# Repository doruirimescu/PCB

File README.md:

# PCB
Printed circuit board projects

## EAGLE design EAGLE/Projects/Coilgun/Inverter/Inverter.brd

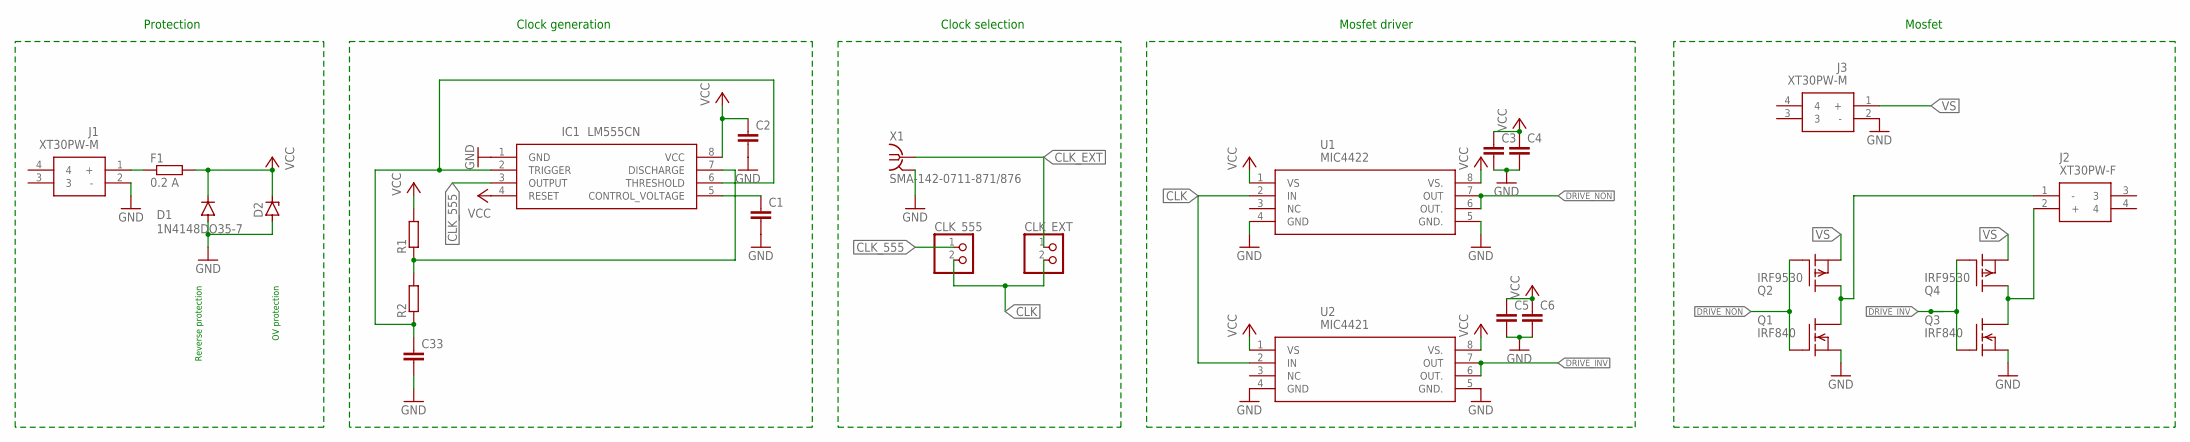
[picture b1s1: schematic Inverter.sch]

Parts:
C1: C-EU025-050X050; C025-050X050
C2, C3, C4, C5, C6, C33: C-EUC0805; C0805
CLK_555: PINHD-1X2; 1X02
CLK_EXT: PINHD-1X2; 1X02
D1: 1N4148DO35-7; DO35-7
D2: ZENER-DIODEDO35Z10; DO35Z10
F1: 0.2 A; M1206
IC1: LM555CN; DIP762W53P254L980H533Q8N
J1, J3: XT30PW-M; XT30PWM
J2: XT30PW-F; XT30PWF
Q1, Q3: IRF840; TO220
Q2, Q4: IRF9530; TO220
R1, R2: R-EU_M0805; M0805
U1: MIC4422; MIC4421
U2: MIC4421
X1: SMA-142-0711-871/876; J502-ND-142-0711-871/876

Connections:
CLK: CLK_555.2, CLK_EXT.2, U1.2 (IN), U2.2 (IN)
CLK_555: CLK_555.1, IC1.3 (OUTPUT)
CLK_EXT: CLK_EXT.1, X1.1
DRIVE_INV: Q3.1 (G), Q4.1 (G), U2.6 (OUT.), U2.7 (OUT)
DRIVE_NON: Q1.1 (G), Q2.1 (G), U1.6 (OUT.), U1.7 (OUT)
GND: C1.2, C2.2, C3.2, C4.2, C5.2, C6.2, C33.2, D1.A, D2.A, IC1.1 (GND), J1.2 (-), J3.2 (-), Q1.3 (S), Q3.3 (S), U1.4 (GND), U1.5 (GND.), U2.4 (GND), U2.5 (GND.), X1.G@1 (2), X1.G@2 (2), X1.G@3 (2), X1.G@4 (2)
unnamed: C33.1, IC1.2 (TRIGGER), IC1.6 (THRESHOLD), R2.1
unnamed: IC1.7 (DISCHARGE), R1.1, R2.2
unnamed: C1.1, IC1.5 (CONTROL_VOLTAGE)
unnamed: J2.1 (-), Q1.2 (D), Q2.2 (D)
unnamed: J2.2 (+), Q3.2 (D), Q4.2 (D)
unnamed: F1.1, J1.1 (+)
VCC: C2.1, C3.1, C4.1, C5.1, C6.1, D1.C, D2.C, F1.2, IC1.4 (RESET), IC1.8 (VCC), R1.2, U1.1 (VS), U1.8 (VS.), U2.1 (VS), U2.8 (VS.)
VS: J3.1 (+), Q2.3 (S), Q4.3 (S)

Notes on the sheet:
Clock generation
Clock selection
Protection
Reverse protection
OV protection
Mosfet driver
Mosfet

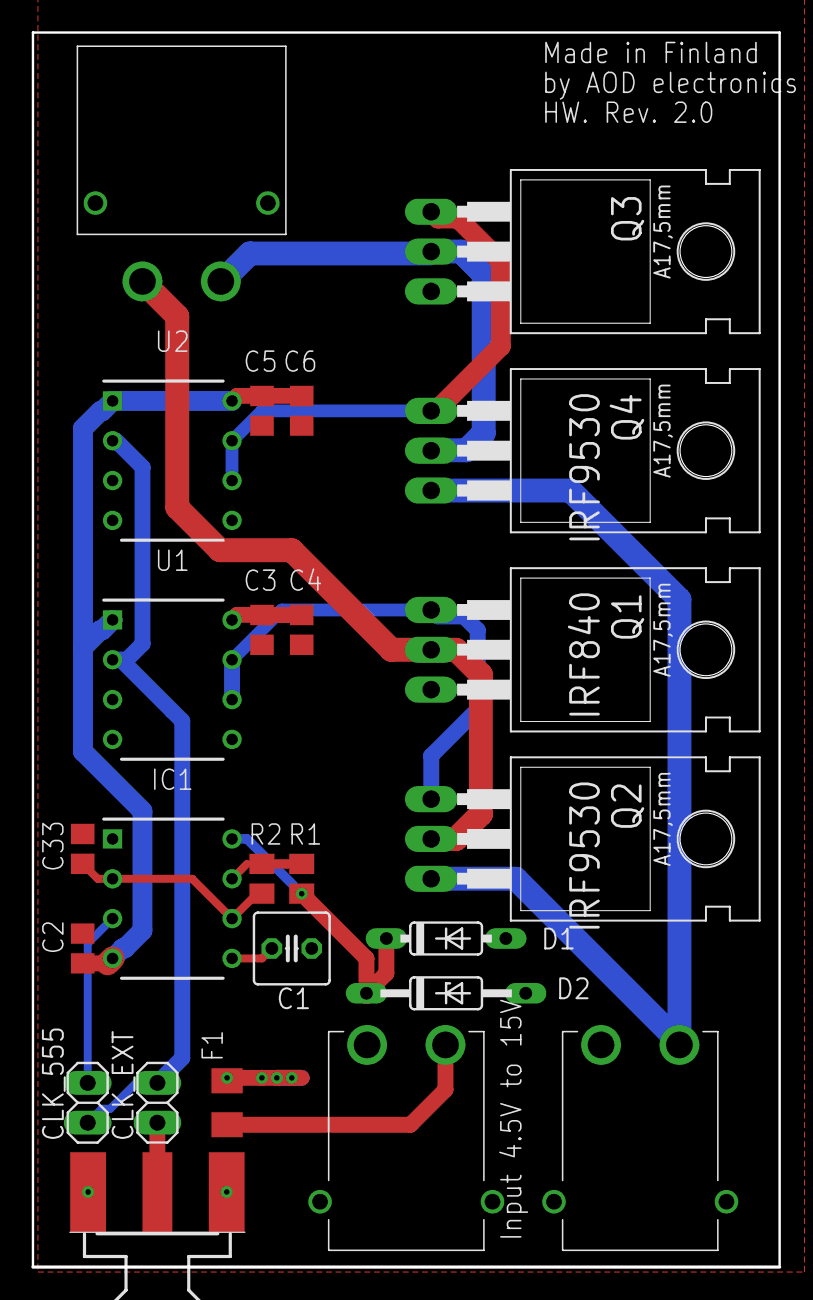
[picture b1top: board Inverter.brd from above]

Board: 2 copper layers, 47.6 x 78.7 mm, 25 parts (0 on the bottom side), 14 nets.

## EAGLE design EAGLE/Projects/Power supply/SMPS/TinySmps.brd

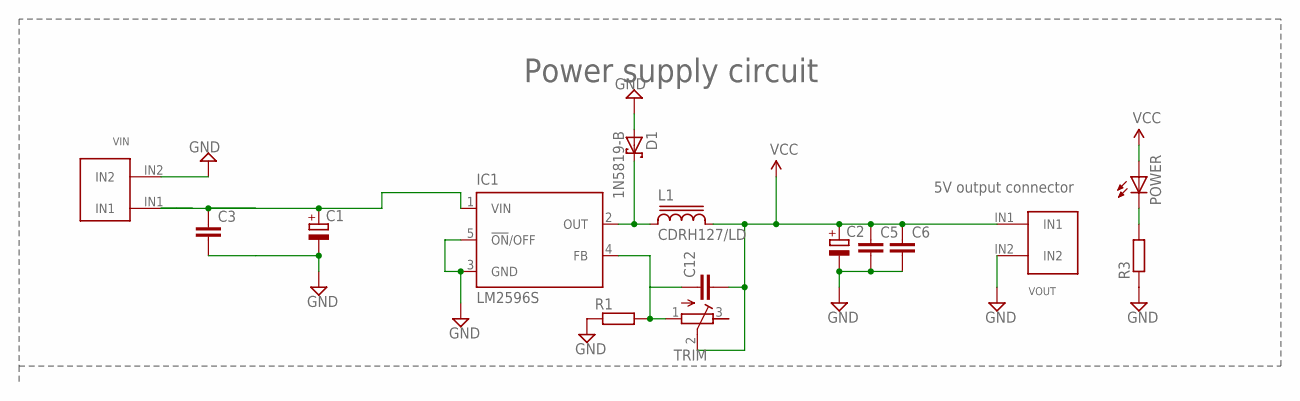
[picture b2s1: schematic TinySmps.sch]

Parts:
C1, C2: CPOL-EUE5-10.5; E5-10,5
C3, C5, C6: C-EUC1206; C1206
C12: C2,5-3; C2.5-3
D1: 1N5819-B; DO41-7.6
IC1: LM2596S; TO263-5
L1: CDRH127/LD
POWER: LEDSML0805; SML0805
R1: R-EU_0204/7; 0204/7
R3: R-EU_R1206; R1206
TRIM: R-TRIMM3296W; RTRIM3296W
VIN: 1X2_5MM
VOUT: 1X2_5MM

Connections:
GND: C1.-, C2.-, C3.2, C5.2, C6.2, D1.A, IC1.3 (GND), IC1.5 (!ON!/OFF), R1.1, R3.1, VIN.IN2, VOUT.IN2
IN: C1.+, C3.1, IC1.1 (VIN), VIN.IN1
unnamed: POWER.C, R3.2
unnamed: D1.C, IC1.2 (OUT), L1.1
unnamed: C12.1, IC1.4 (FB), R1.2, TRIM.1 (A)
VCC: C2.+, C5.1, C6.1, C12.2, L1.2, POWER.A, TRIM.2 (S), VOUT.IN1

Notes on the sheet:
Power supply circuit
5V output connector

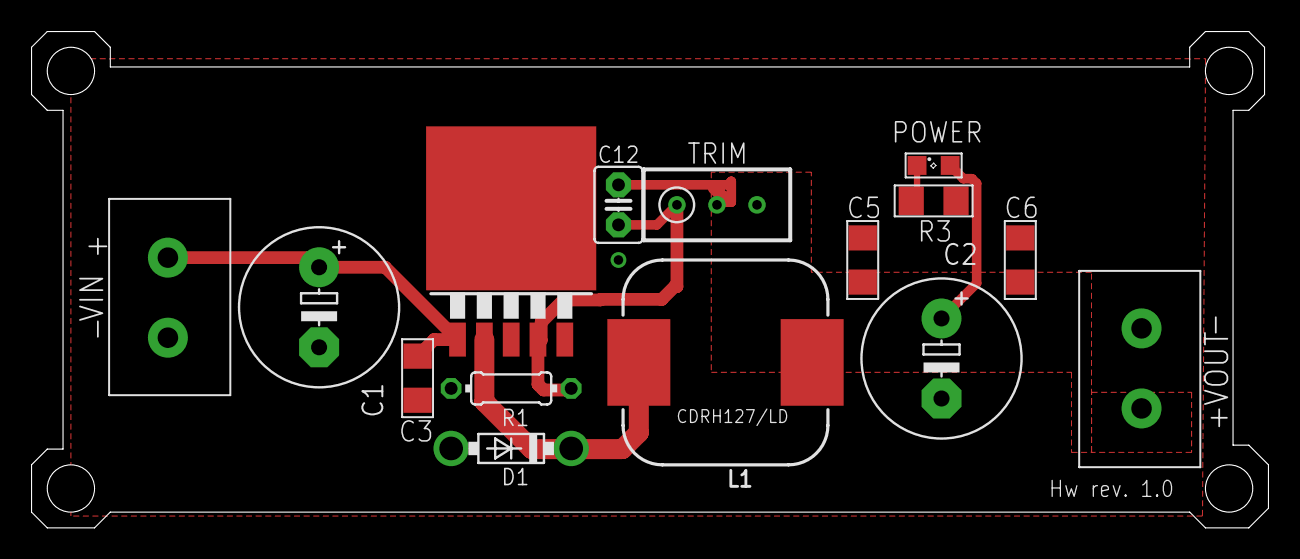
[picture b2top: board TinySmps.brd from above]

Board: 2 copper layers, 78.5 x 31.5 mm, 15 parts (0 on the bottom side), 6 nets.

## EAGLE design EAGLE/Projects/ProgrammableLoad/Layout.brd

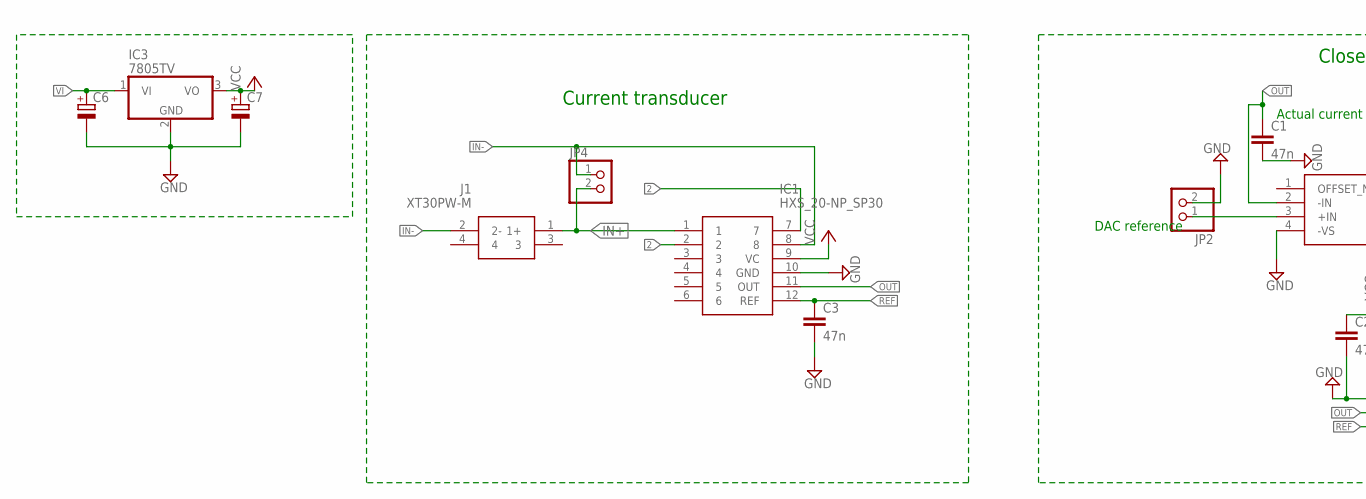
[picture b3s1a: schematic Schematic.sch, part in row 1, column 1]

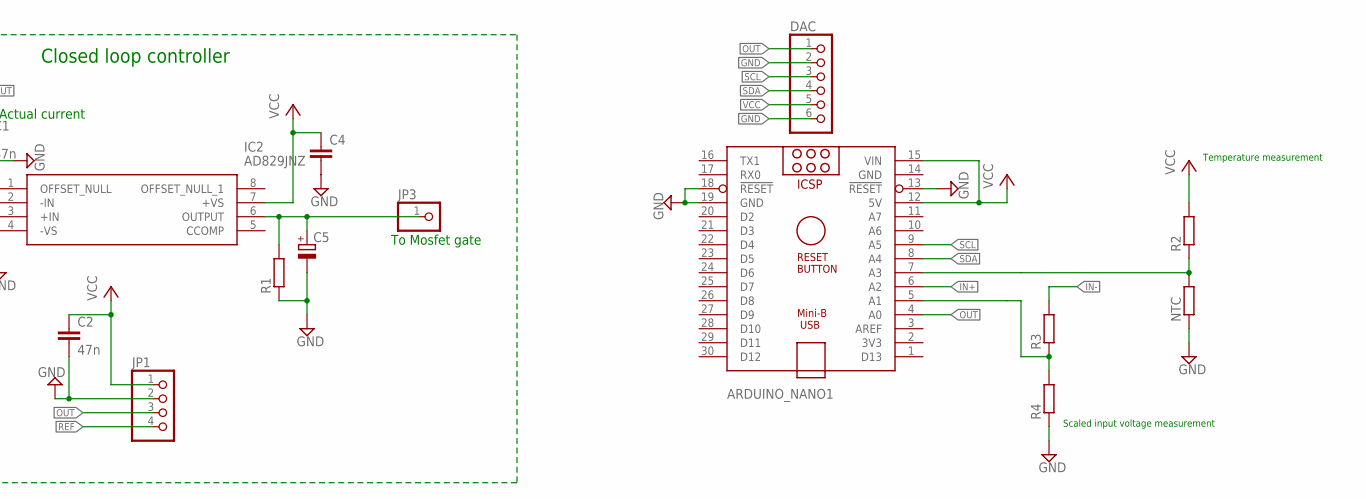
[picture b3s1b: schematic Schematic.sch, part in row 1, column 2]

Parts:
ARDUINO_NANO1: ARDUINO_NANO
C1, C2, C3: 47n; C2.5-6
C4: C-EUC0805; C0805
C5: CPOL-EUE5-6; E5-6
C6, C7: CPOL-EUE2.5-5; E2,5-5
DAC: PINHD-1X6; 1X06
IC1: HXS_20-NP_SP30; HXS_20-NP/SP30
IC2: AD829JNZ; DIP794W56P254L959H533Q8N
IC3: 7805TV; TO220V
J1: XT30PW-M; XT30PWM
JP1: PINHD-1X4; 1X04
JP2, JP4: PINHD-1X2; 1X02
JP3: PINHD-1X1; 1X01
NTC: R0207/10; 0207/10
R1, R2: R0207/10; 0207/10
R3, R4: R-EU_R1206; R1206

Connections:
2: IC1.2, IC1.7
GND: ARDUINO_NANO1.13 (!RESET), ARDUINO_NANO1.14 (GND), ARDUINO_NANO1.18 (!RESET), ARDUINO_NANO1.19 (GND), C1.2, C2.2, C3.2, C4.2, C5.-, C6.-, C7.-, DAC.2, DAC.6, IC1.10 (GND), IC2.4 (-VS), IC3.2 (GND), JP1.2, JP2.2, NTC.1, R1.1, R4.1
IN+: ARDUINO_NANO1.6 (A2), IC1.1, J1.1 (1+), JP4.2
IN-: IC1.8, J1.2 (2-), JP4.1, R3.2
unnamed: C5.+, IC2.6 (OUTPUT), JP3.1, R1.2
unnamed: ARDUINO_NANO1.5 (A1), R3.1, R4.2
unnamed: IC2.3 (+IN), JP2.1
unnamed: ARDUINO_NANO1.7 (A3), NTC.2, R2.1
OUT: ARDUINO_NANO1.4 (A0), C1.1, DAC.1, IC1.11 (OUT), IC2.2 (-IN), JP1.3
REF: C3.1, IC1.12 (REF), JP1.4
SCL: ARDUINO_NANO1.9 (A5), DAC.3
SDA: ARDUINO_NANO1.8 (A4), DAC.4
VCC: ARDUINO_NANO1.12 (5V), ARDUINO_NANO1.15 (VIN), C2.1, C4.1, C7.+, DAC.5, IC1.9 (VC), IC2.7 (+VS), IC3.3 (VO), JP1.1, R2.2
VI: C6.+, IC3.1 (VI)

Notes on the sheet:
DAC reference
Actual current
To Mosfet gate
Current transducer
Closed loop controller
Temperature measurement
Scaled input voltage measurement

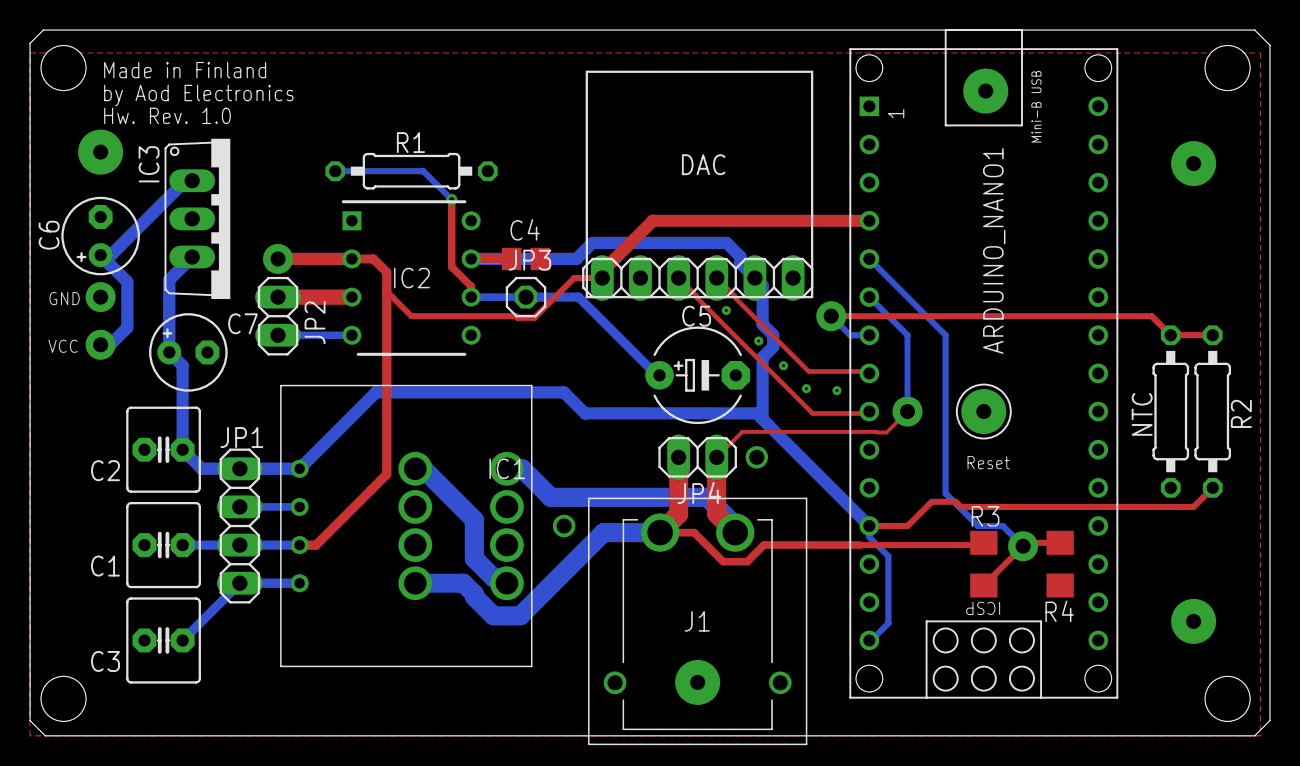
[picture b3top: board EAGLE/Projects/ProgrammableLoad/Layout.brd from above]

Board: 2 copper layers, 82.5 x 47.0 mm, 22 parts (0 on the bottom side), 14 nets.

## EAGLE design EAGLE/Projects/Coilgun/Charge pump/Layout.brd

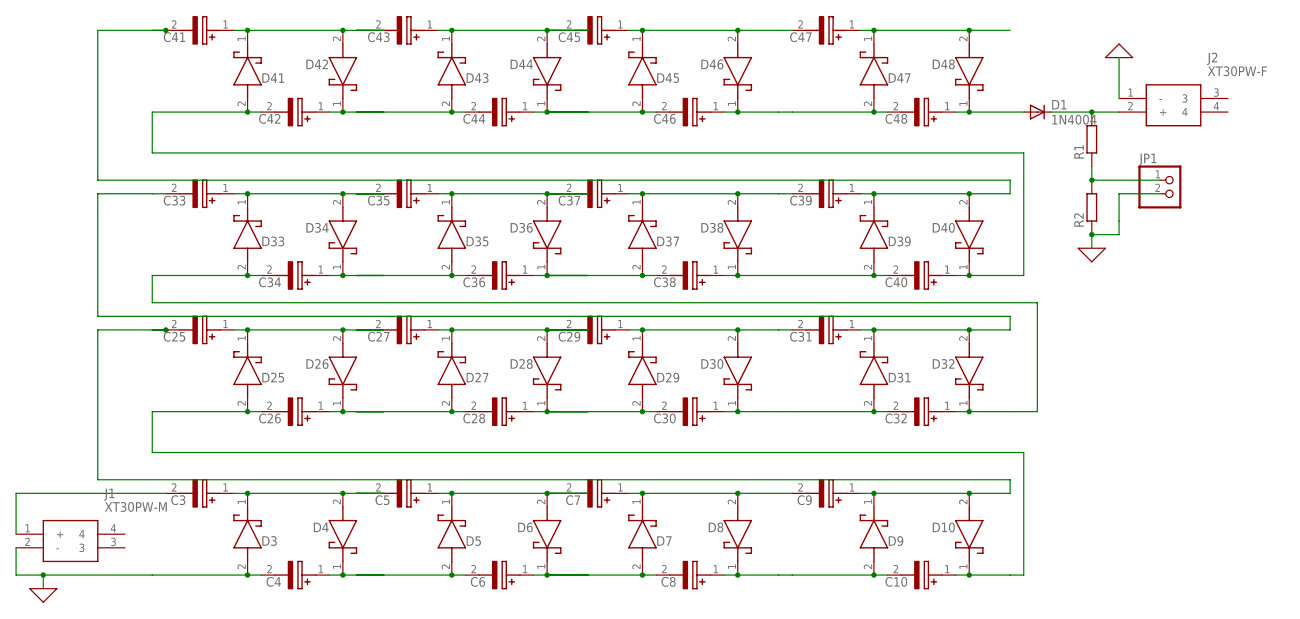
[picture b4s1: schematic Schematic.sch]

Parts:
C3, C4, C5, C6, C7, C8, C9, C10, C25, C26, C27, C28, C29, C30, C31, C32, C33, C34, C35, C36, C37, C38, C39, C40, C41, C42, C43, C44, C45, C46, C47, C48: AFK108M25H32T-F; CAPAE1350X1400N
D1: 1N4004; DO41-10
D3, D4, D5, D6, D7, D8, D9, D10, D25, D26, D27, D28, D29, D30, D31, D32, D33, D34, D35, D36, D37, D38, D39, D40, D41, D42, D43, D44, D45, D46, D47, D48: PMEG3050EP,115; PMEG3050EP115
J1: XT30PW-M; XT30PWM
J2: XT30PW-F; XT30PWF
JP1: PINHD-1X2; 1X02
R1, R2: RR0603; R0603

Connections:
0: C4.2 (-), D3.2 (A), J1.2 (-), J2.1 (-), JP1.2, R2.1
unnamed: D1.C, J2.2 (+), R1.2
unnamed: JP1.1, R1.1, R2.2
unnamed: C3.1 (+), C5.2 (-), D3.1 (K), D4.2 (A)
unnamed: C3.2 (-), J1.1 (+)
unnamed: C5.1 (+), C7.2 (-), D5.1 (K), D6.2 (A)
unnamed: C4.1 (+), C6.2 (-), D4.1 (K), D5.2 (A)
unnamed: C6.1 (+), C8.2 (-), D6.1 (K), D7.2 (A)
unnamed: C9.1 (+), C25.2 (-), D9.1 (K), D10.2 (A)
unnamed: C8.1 (+), C10.2 (-), D8.1 (K), D9.2 (A)
unnamed: C10.1 (+), C26.2 (-), D10.1 (K), D25.2 (A)
unnamed: C7.1 (+), C9.2 (-), D7.1 (K), D8.2 (A)
unnamed: C33.1 (+), C35.2 (-), D33.1 (K), D34.2 (A)
unnamed: C25.1 (+), C27.2 (-), D25.1 (K), D26.2 (A)
unnamed: C31.1 (+), C33.2 (-), D31.1 (K), D32.2 (A)
unnamed: C35.1 (+), C37.2 (-), D35.1 (K), D36.2 (A)
unnamed: C27.1 (+), C29.2 (-), D27.1 (K), D28.2 (A)
unnamed: C26.1 (+), C28.2 (-), D26.1 (K), D27.2 (A)
unnamed: C28.1 (+), C30.2 (-), D28.1 (K), D29.2 (A)
unnamed: C30.1 (+), C32.2 (-), D30.1 (K), D31.2 (A)
unnamed: C32.1 (+), C34.2 (-), D32.1 (K), D33.2 (A)
unnamed: C29.1 (+), C31.2 (-), D29.1 (K), D30.2 (A)
unnamed: C34.1 (+), C36.2 (-), D34.1 (K), D35.2 (A)
unnamed: C36.1 (+), C38.2 (-), D36.1 (K), D37.2 (A)
unnamed: C39.1 (+), C41.2 (-), D39.1 (K), D40.2 (A)
unnamed: C38.1 (+), C40.2 (-), D38.1 (K), D39.2 (A)
unnamed: C40.1 (+), C42.2 (-), D40.1 (K), D41.2 (A)
unnamed: C37.1 (+), C39.2 (-), D37.1 (K), D38.2 (A)
unnamed: C41.1 (+), C43.2 (-), D41.1 (K), D42.2 (A)
unnamed: C43.1 (+), C45.2 (-), D43.1 (K), D44.2 (A)
unnamed: C42.1 (+), C44.2 (-), D42.1 (K), D43.2 (A)
unnamed: C44.1 (+), C46.2 (-), D44.1 (K), D45.2 (A)
unnamed: C47.1 (+), D47.1 (K), D48.2 (A)
unnamed: C46.1 (+), C48.2 (-), D46.1 (K), D47.2 (A)
unnamed: C48.1 (+), D1.A, D48.1 (K)
unnamed: C45.1 (+), C47.2 (-), D45.1 (K), D46.2 (A)

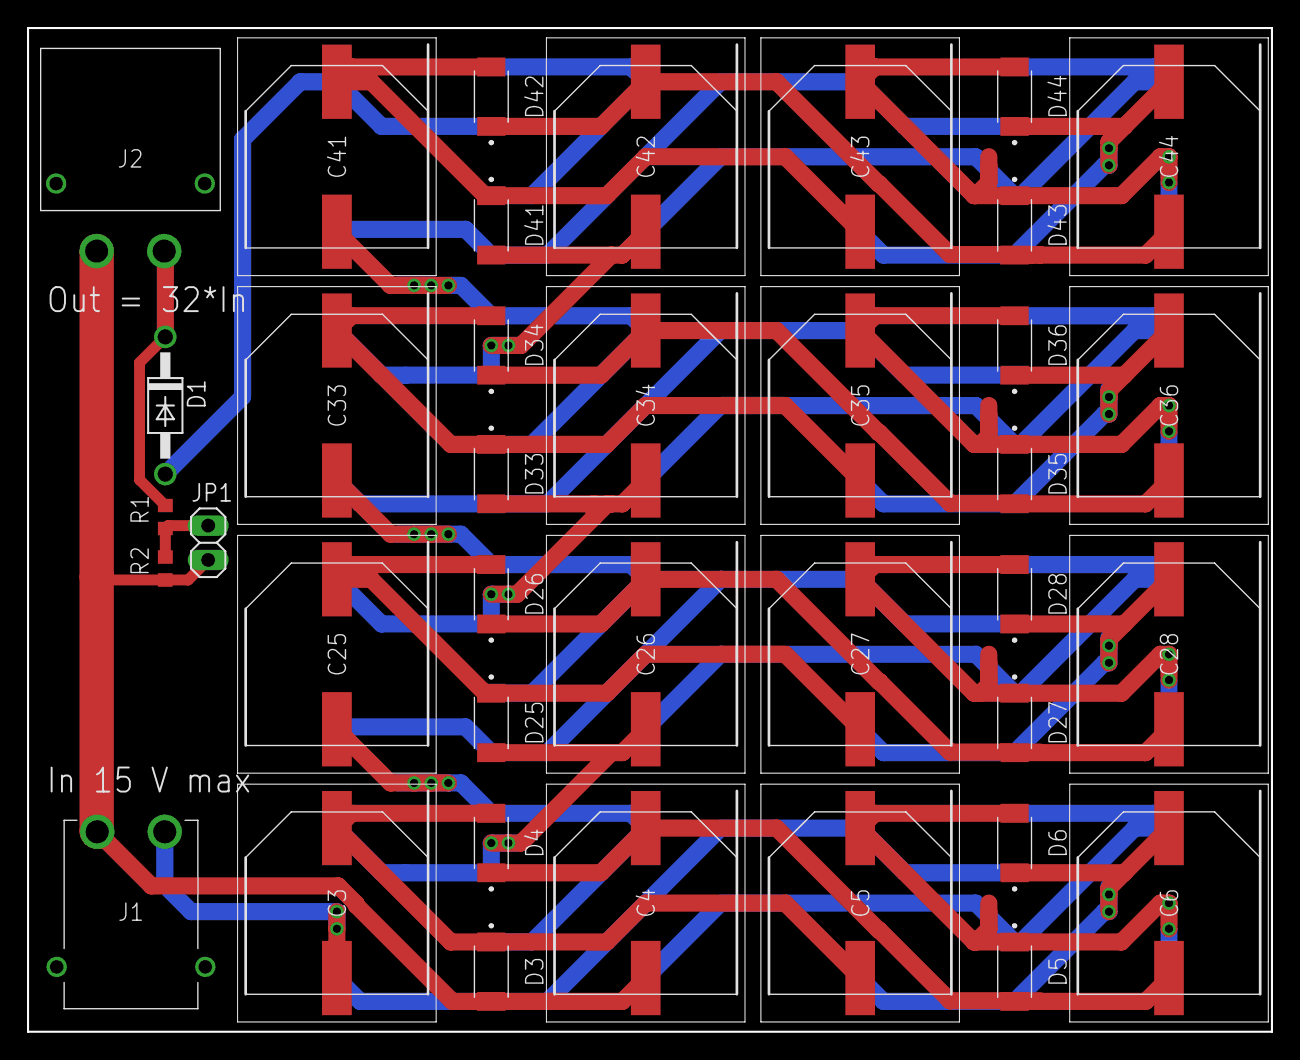
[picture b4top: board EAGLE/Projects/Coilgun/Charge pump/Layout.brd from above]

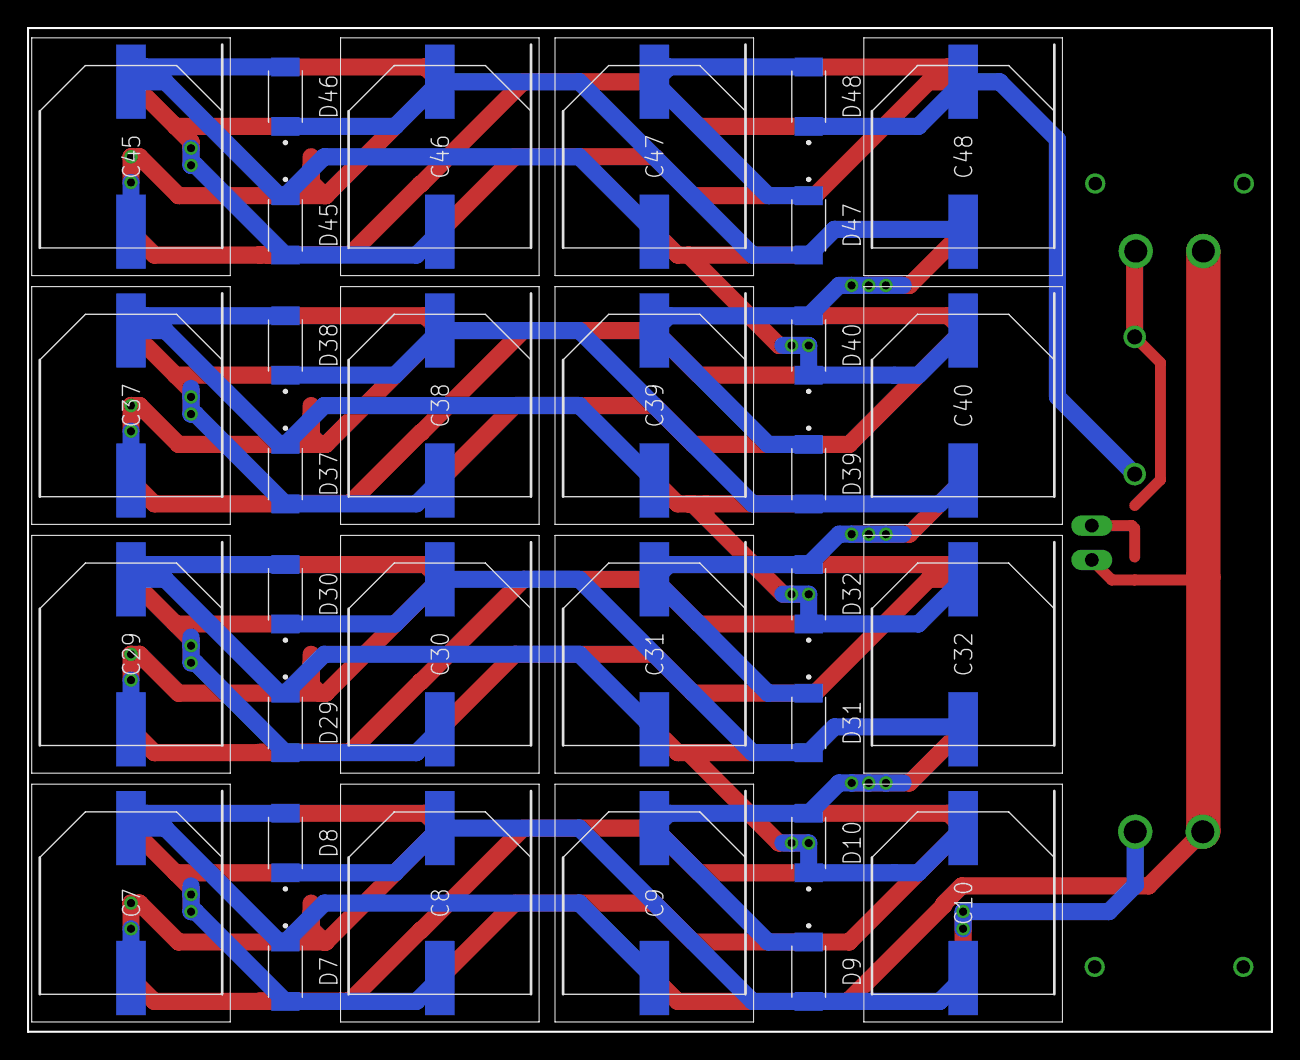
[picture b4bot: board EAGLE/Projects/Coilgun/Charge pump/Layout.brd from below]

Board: 2 copper layers, 92.1 x 74.3 mm, 70 parts (32 on the bottom side), 36 nets.

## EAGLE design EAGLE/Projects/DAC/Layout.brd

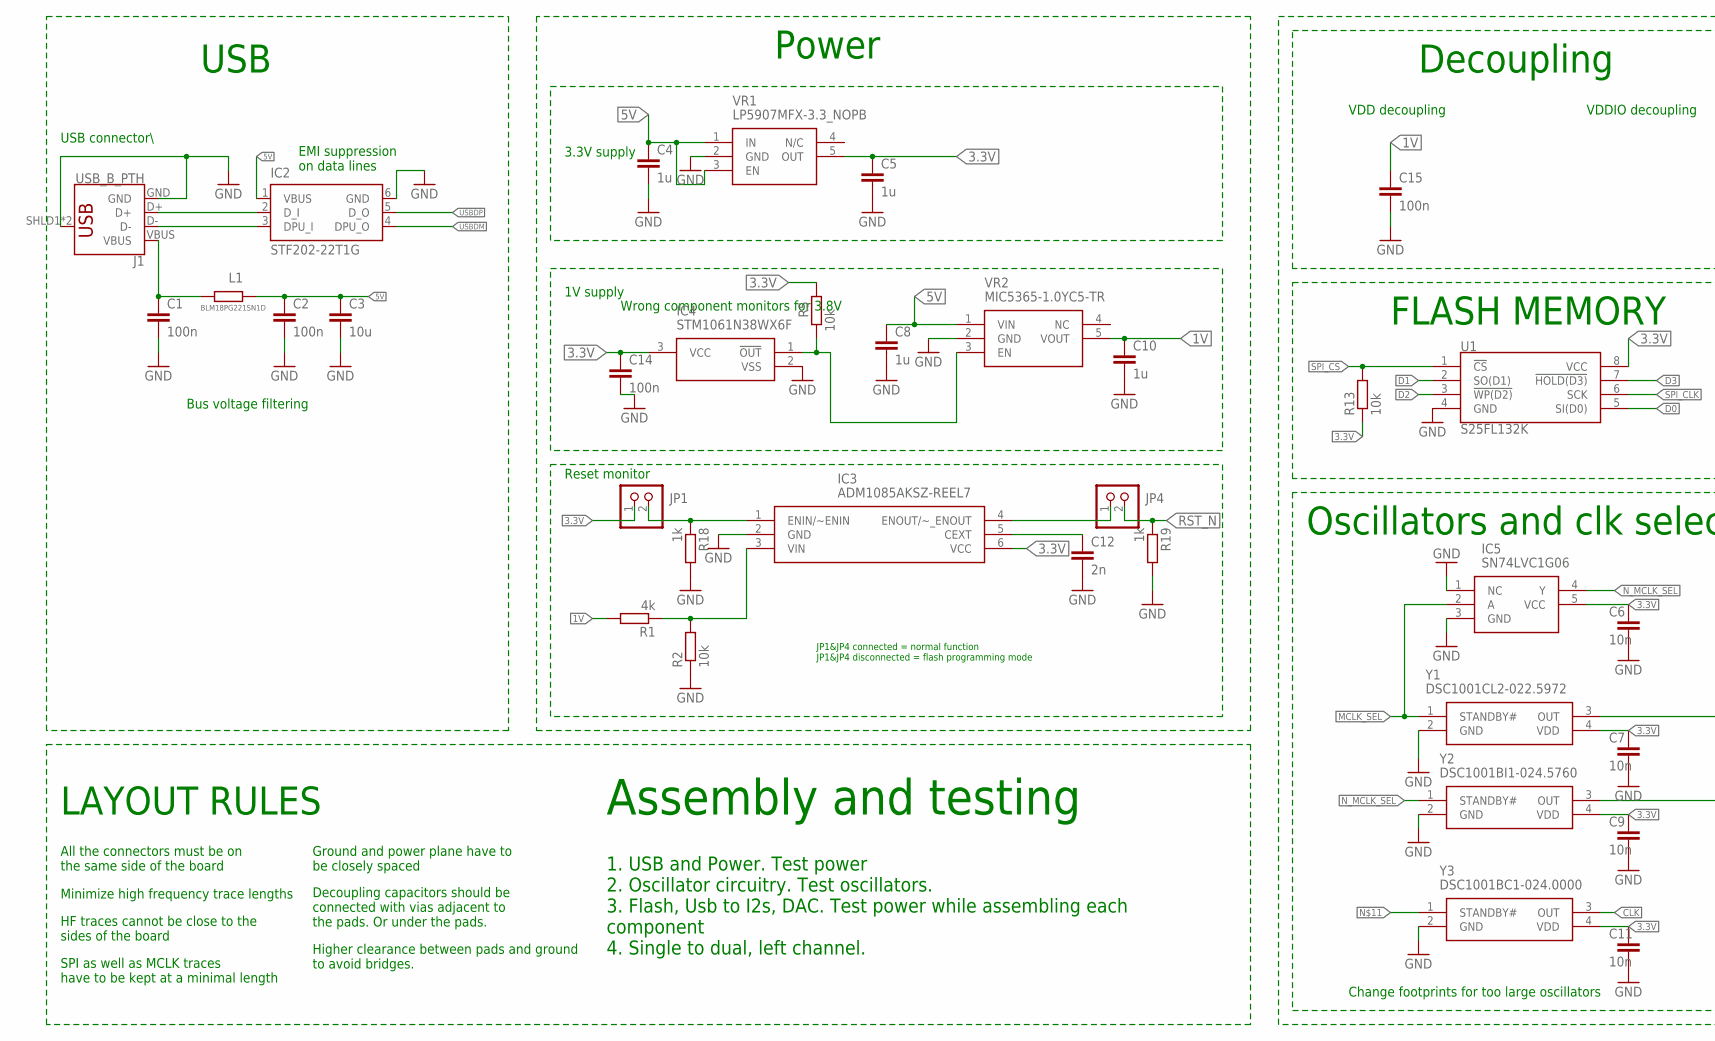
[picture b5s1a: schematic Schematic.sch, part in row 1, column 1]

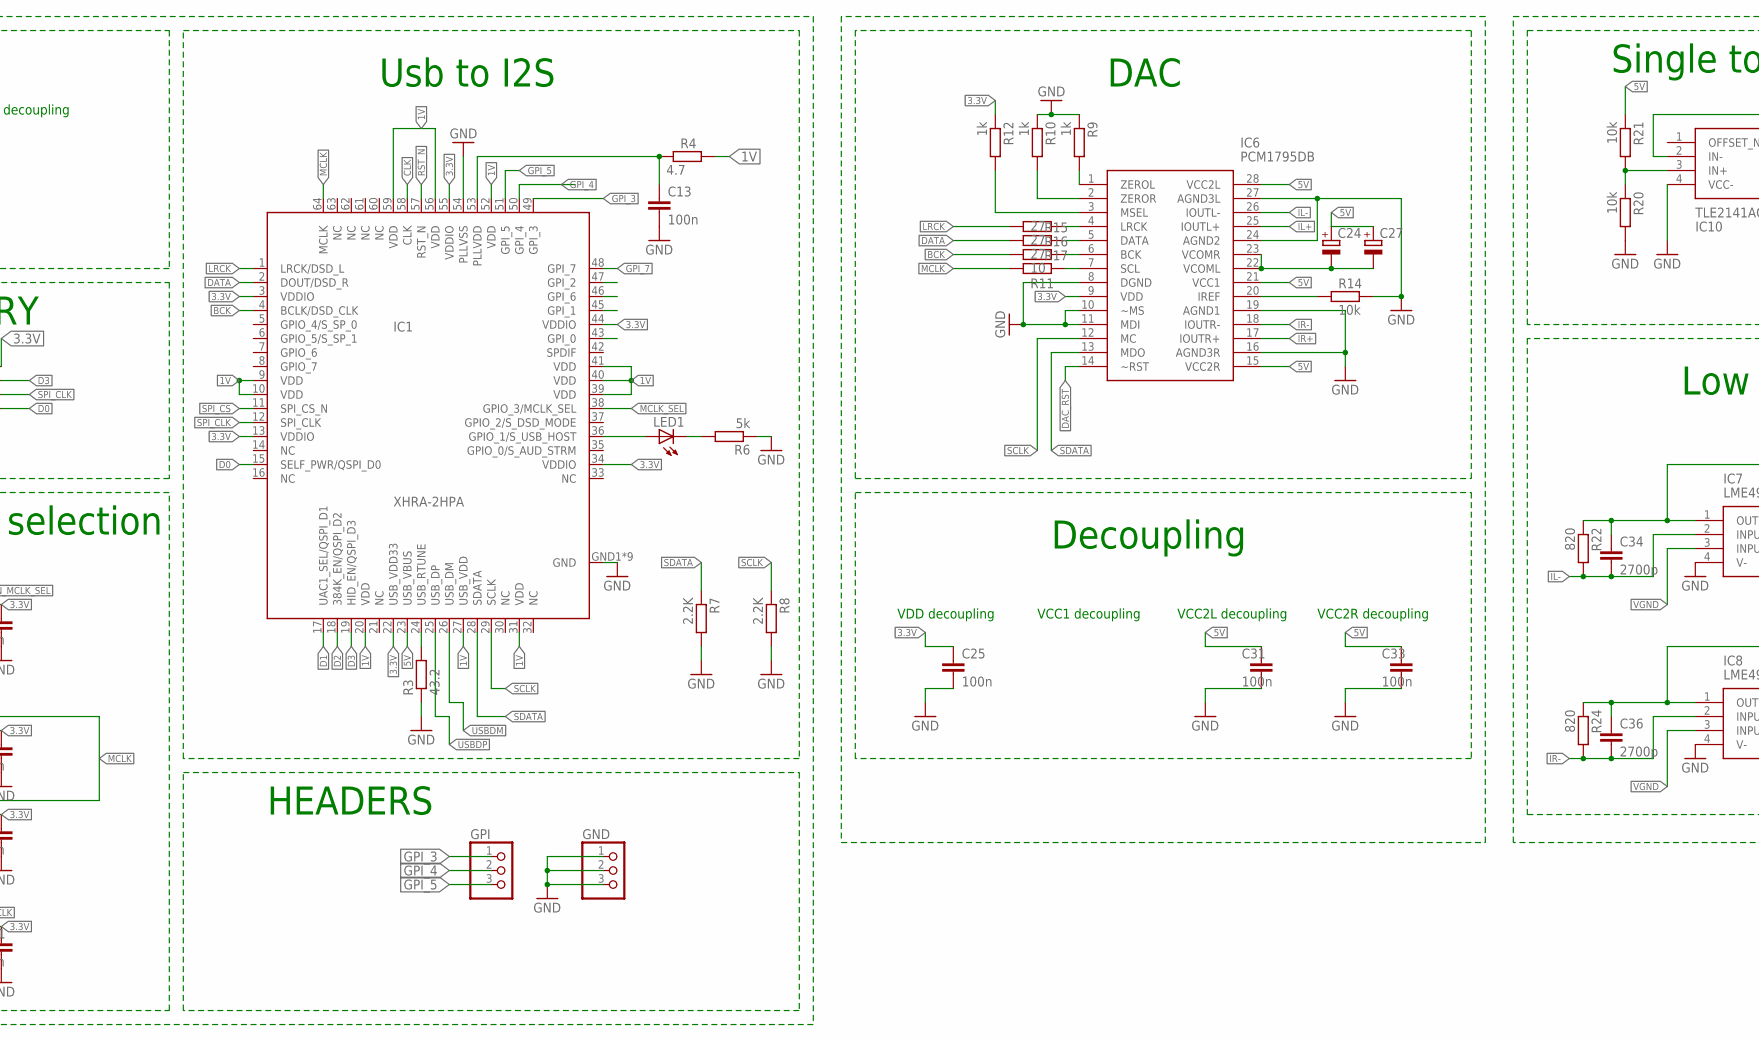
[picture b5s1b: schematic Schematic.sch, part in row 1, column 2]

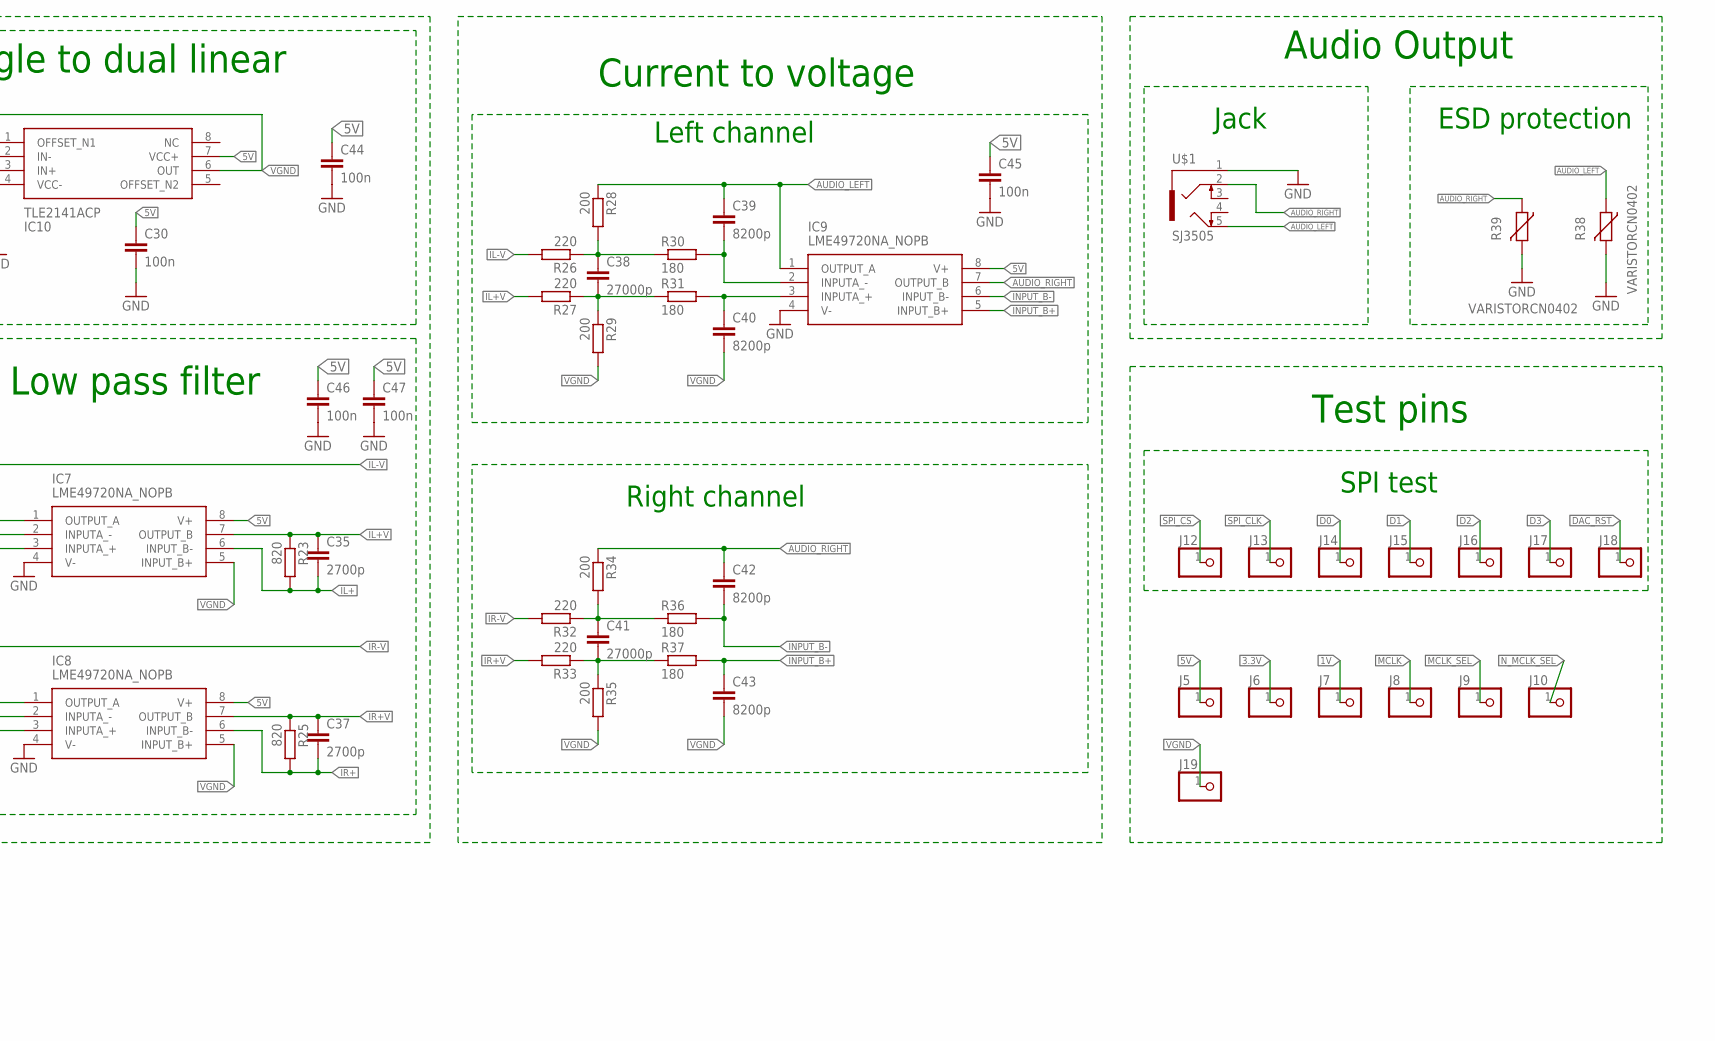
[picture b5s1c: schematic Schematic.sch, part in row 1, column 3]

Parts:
C1, C2, C13, C14, C15, C25, C30, C31, C33, C44, C45, C46, C47: 100n; C0603K; MPN A104M15X7RF5TAA
C3: 10u; C0603K
C4, C5, C8, C10: 1u; C0603K
C6, C7, C9, C11: 10n; C0603K
C12: 2n; C0603K
C24, C27: CPOL-EUSANYO_SMD_B6; SANYO-OSCON_SMD_B6
C34, C35, C36, C37: 2700p; C0805
C38, C41: 27000p; C1210
C39, C40, C42, C43: 8200p; C0805
GND: PINHD-1X3; 1X03
GPI: PINHD-1X3; 1X03
IC1: XHRA-2HPA; TQFP64
IC2: STF202-22T1G; SOT23-6
IC3: ADM1085AKSZ-REEL7; SOT65P210X110-6N
IC4: STM1061N38WX6F; SOT103P237X112-3N
IC5: SN74LVC1G06; SOT95P280X145-5N
IC6: PCM1795DB; SOP65P780X200-28N
IC7, IC8, IC9: LME49720NA_NOPB; DIP794W53P254L959H508Q8N
IC10: TLE2141ACP; DIP794W53P254L959H508Q8N
J1: USB_B_PTH; USB-B-PTH
J5, J6, J7, J8, J9, J10, J12, J13, J14, J15, J16, J17, J18, J19: PINHD-1X1; 1X01
JP1, JP4: PINHD-1X2; 1X02
L1: BLM18PG221SN1D; R0603
LED1: LEDSML0603; SML0603
R1: 4k; R0603
R2, R5, R13, R14, R20, R21: 10k; R0603
R3: 43.2; R0603
R4: 4.7; R0603
R6: 5k; R0603
R7, R8: 2.2K; R0603
R9, R10, R12, R18, R19: 1k; R0603
R11: 10; R0603
R15, R16, R17: 27; R0603
R22, R23, R24, R25: 820; R0603
R26, R27, R32, R33: 220; R0603
R28, R29, R34, R35: 200; R0603
R30, R31, R36, R37: 180; R0603
R38, R39: VARISTORCN0402; CT/CN0402
U1: S25FL132K; SO08
U$1: SJ3505
VR1: LP5907MFX-3.3_NOPB; SOT95P280X145-5N
VR2: MIC5365-1.0YC5-TR; SOT65P210X110-5N
Y1: DSC1001CL2-022.5972; DSC1001DL50250000T
Y2: DSC1001BI1-024.5760; DSC1001DL50250000T
Y3: DSC1001BC1-024.0000; DSC1001DL50250000T

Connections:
1V: C10.1, C15.1, IC1.9 (VDD), IC1.10 (VDD), IC1.20 (VDD), IC1.27 (USB_VDD), IC1.31 (VDD), IC1.39 (VDD), IC1.40 (VDD), IC1.41 (VDD), IC1.52 (VDD), IC1.56 (VDD), IC1.59 (VDD), J7.1, R1.2, R4.2, VR2.5 (VOUT)
3.3V: C5.1, C6.1, C7.1, C9.1, C11.1, C14.1, C25.1, IC1.3 (VDDIO), IC1.13 (VDDIO), IC1.22 (USB_VDD33), IC1.34 (VDDIO), IC1.44 (VDDIO), IC1.55 (VDDIO), IC3.6 (VCC), IC4.3 (VCC), IC5.5 (VCC), IC6.9 (VDD), J6.1, JP1.1, R5.2, R12.1, R13.1, U1.8 (VCC), VR1.5 (OUT), Y1.4 (VDD), Y2.4 (VDD), Y3.4 (VDD)
5V: C2.1, C3.1, C4.1, C8.1, C24.+, C27.+, C30.1, C31.1, C33.1, C44.1, C45.1, C46.1, C47.1, IC1.23 (USB_VBUS), IC2.1 (VBUS), IC6.15 (VCC2R), IC6.21 (VCC1), IC6.28 (VCC2L), IC7.8 (V+), IC8.8 (V+), IC9.8 (V+), IC10.7 (VCC+), J5.1, L1.2, R21.1, VR1.1 (IN), VR1.3 (EN), VR2.1 (VIN)
AUDIO_LEFT: C39.1, IC9.1 (OUTPUT_A), R28.1, R38.1, U$1.5
AUDIO_RIGHT: C42.1, IC9.7 (OUTPUT_B), R34.1, R39.1, U$1.2
BCK: IC1.4 (BCLK/DSD_CLK), R17.1
CLK: IC1.58 (CLK), Y3.3 (OUT)
D0: IC1.15 (SELF_PWR/QSPI_D0), J14.1, U1.5 (SI(D0))
D1: IC1.17 (UAC1_SEL/QSPI_D1), J15.1, U1.2 (SO(D1))
D2: IC1.18 (384K_EN/QSPI_D2), J16.1, U1.3 (!WP(D2))
D3: IC1.19 (HID_EN/QSPI_D3), J17.1, U1.7 (!HOLD(D3))
DAC_RST: IC6.14 (~RST), J18.1
DATA: IC1.2 (DOUT/DSD_R), R16.1
DM_I: IC2.3 (DPU_I), J1.D-
DP_I: IC2.2 (D_I), J1.D+
GND: C1.2, C2.2, C3.2, C4.2, C5.2, C6.2, C7.2, C8.2, C9.2, C10.2, C11.2, C12.2, C13.2, C14.2, C15.2, C25.2, C30.2, C31.2, C33.2, C44.2, C45.2, C46.2, C47.2, GND.1, GND.2, GND.3, IC1.54 (PLLVSS), IC1.GND1 (GND), IC1.GND2 (GND), IC1.GND3 (GND), IC1.GND4 (GND), IC1.GND5 (GND), IC1.GND6 (GND), IC1.GND7 (GND), IC1.GND8 (GND), IC1.GND9 (GND), IC2.6 (GND), IC3.2 (GND), IC4.2 (VSS), IC5.1 (NC), IC5.3 (GND), IC6.8 (DGND), IC6.10 (~MS), IC6.11 (MDI), IC6.16 (AGND3R), IC6.19 (AGND1), IC6.24 (AGND2), IC6.27 (AGND3L), IC7.4 (V-), IC8.4 (V-), IC9.4 (V-), IC10.4 (VCC-), J1.GND, J1.SHLD1 (SHIELD), J1.SHLD2 (SHIELD), R2.1, R3.1, R6.1, R7.2, R8.2, R9.1, R10.1, R14.1, R18.2, R19.2, R20.2, R38.2, R39.2, U1.4 (GND), U$1.1, VR1.2 (GND), VR2.2 (GND), Y1.2 (GND), Y2.2 (GND), Y3.2 (GND)
GPI_0: IC1.43 (GPI_0)
GPI_1: IC1.45 (GPI_1)
GPI_2: IC1.47 (GPI_2)
GPI_3: GPI.1, IC1.49 (GPI_3)
GPI_4: GPI.2, IC1.50 (GPI_4)
GPI_5: GPI.3, IC1.51 (GPI_5)
GPI_6: IC1.46 (GPI_6)
GPI_7: IC1.48 (GPI_7)
IL+: C35.2, IC6.25 (IOUTL+), IC7.6 (INPUT_B-), R23.2
IL+V: C35.1, IC7.7 (OUTPUT_B), R23.1, R27.2
IL-: C34.2, IC6.26 (IOUTL-), IC7.2 (INPUTA_-), R22.2
IL-V: C34.1, IC7.1 (OUTPUT_A), R22.1, R26.2
INPUT_B+: C43.1, IC9.5 (INPUT_B+), R37.2
INPUT_B-: C42.2, IC9.6 (INPUT_B-), R36.2
IR+: C37.2, IC6.17 (IOUTR+), IC8.6 (INPUT_B-), R25.2
IR+V: C37.1, IC8.7 (OUTPUT_B), R25.1, R33.2
IR-: C36.2, IC6.18 (IOUTR-), IC8.2 (INPUTA_-), R24.2
IR-V: C36.1, IC8.1 (OUTPUT_A), R24.1, R32.2
LRCK: IC1.1 (LRCK/DSD_L), R15.1
MCLK: IC1.64 (MCLK), J8.1, R11.2, Y1.3 (OUT), Y2.3 (OUT)
MCLK_SEL: IC1.38 (GPIO_3/MCLK_SEL), IC5.2 (A), J9.1, Y1.1 (STANDBY#)
unnamed: C1.1, J1.VBUS, L1.1
unnamed: C12.1, IC3.5 (CEXT)
unnamed: IC3.3 (VIN), R1.1, R2.2
unnamed: IC1.24 (USB_RTUNE), R3.2
unnamed: C13.1, IC1.53 (PLLVDD), R4.1
unnamed: IC4.1 (!OUT), R5.1, VR2.3 (EN)
unnamed: IC1.36 (GPIO_1/S_USB_HOST), LED1.A
unnamed: LED1.C, R6.2
unnamed: IC6.1 (ZEROL), R9.2
unnamed: IC6.7 (SCL), R11.1
unnamed: IC6.2 (ZEROR), R10.2
unnamed: IC6.3 (MSEL), R12.2
unnamed: IC6.20 (IREF), R14.2
unnamed: IC6.4 (LRCK), R15.2
unnamed: IC6.6 (BCK), R17.2
unnamed: IC6.5 (DATA), R16.2
unnamed: IC3.1 (ENIN/~ENIN), JP1.2, R18.1
unnamed: IC3.4 (ENOUT/~_ENOUT), JP4.1
unnamed: C24.-, C27.-, IC6.22 (VCOML), IC6.23 (VCOMR)
unnamed: IC10.3 (IN+), R20.1, R21.2
unnamed: C38.1, R26.1, R28.2, R30.1
unnamed: C38.2, R27.1, R29.1, R31.1
unnamed: C40.1, IC9.3 (INPUTA_+), R31.2
unnamed: C39.2, IC9.2 (INPUTA_-), R30.2
unnamed: C41.1, R32.1, R34.2, R36.1
unnamed: C41.2, R33.1, R35.1, R37.1
N_MCLK_SEL: IC5.4 (Y), J10.1, Y2.1 (STANDBY#)
RST_N: IC1.57 (RST_N), JP4.2, R19.1
SCLK: IC1.29 (SCLK), IC6.12 (MC), R8.1
SDATA: IC1.28 (SDATA), IC6.13 (MDO), R7.1
SPI_CLK: IC1.12 (SPI_CLK), J13.1, U1.6 (SCK)
SPI_CS: IC1.11 (SPI_CS_N), J12.1, R13.2, U1.1 (!CS)
USBDM: IC1.26 (USB_DM), IC2.4 (DPU_O)
USBDP: IC1.25 (USB_DP), IC2.5 (D_O)
VGND: C40.2, C43.2, IC7.3 (INPUTA_+), IC7.5 (INPUT_B+), IC8.3 (INPUTA_+), IC8.5 (INPUT_B+), IC10.2 (IN-), IC10.6 (OUT), J19.1, R29.2, R35.2

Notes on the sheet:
USB
EMI suppression on data lines
USB connector\
Bus voltage filtering
Power
3.3V supply
1V supply
Reset monitor
VDD decoupling
VDDIO decoupling
FLASH MEMORY
Oscillators and clk selection
HEADERS
DAC
LAYOUT RULES
All the connectors must be on the same side of the board
Minimize high frequency trace lengths
HF traces cannot be close to the sides of the board
SPI as well as MCLK traces have to be kept at a minimal length
Ground and power plane have to be closely spaced
Decoupling capacitors should be connected with vias adjacent to the pads. Or under the pads.
VCC2L decoupling
VCC1 decoupling
VCC2R decoupling
JP1&JP4 connected = normal function JP1&JP4 disconnected = flash programming mode
Decoupling
Usb to I2S
Single to dual linear
Low pass filter
Current to voltage
Assembly and testing
1. USB and Power. Test power 2. Oscillator circuitry. Test oscillators. 3. Flash, Usb to I2s, DAC. Test power while assembling each component 4. Single to dual, left channel.
Audio Output
Test pins
Higher clearance between pads and ground to avoid bridges.
Right channel
Left channel
ESD protection
Jack
SPI test

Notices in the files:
parts and their libraries:
SparkFun-Connectors: Licensing: Creative Commons ShareAlike 4.0 International - https://creativecommons.org/licenses/by-sa/4.0
inductor-sumida: Copyright (C) 2008, Bob Starr
